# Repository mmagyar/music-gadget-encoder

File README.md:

# Music gadget base on STM32G070 MCU

# Modes of operation
 - Step sequencer
 - Midi controller
 
# Software
This project is built on a basic STM32Cube generated base, with using LL drivers.
TrueSTUDIO for STM32 is used for building and debugging.

# Hardware
The schematics and the pcb is designed with KiCad.
This is not a pcb that can be easily done at home, but most cheap chinease pcb manufaturers will be able to make them for you.
It uses 0805 SMD components, soldering this together is not for beginner.

# Picture of the prototype
In step sequencer mode:

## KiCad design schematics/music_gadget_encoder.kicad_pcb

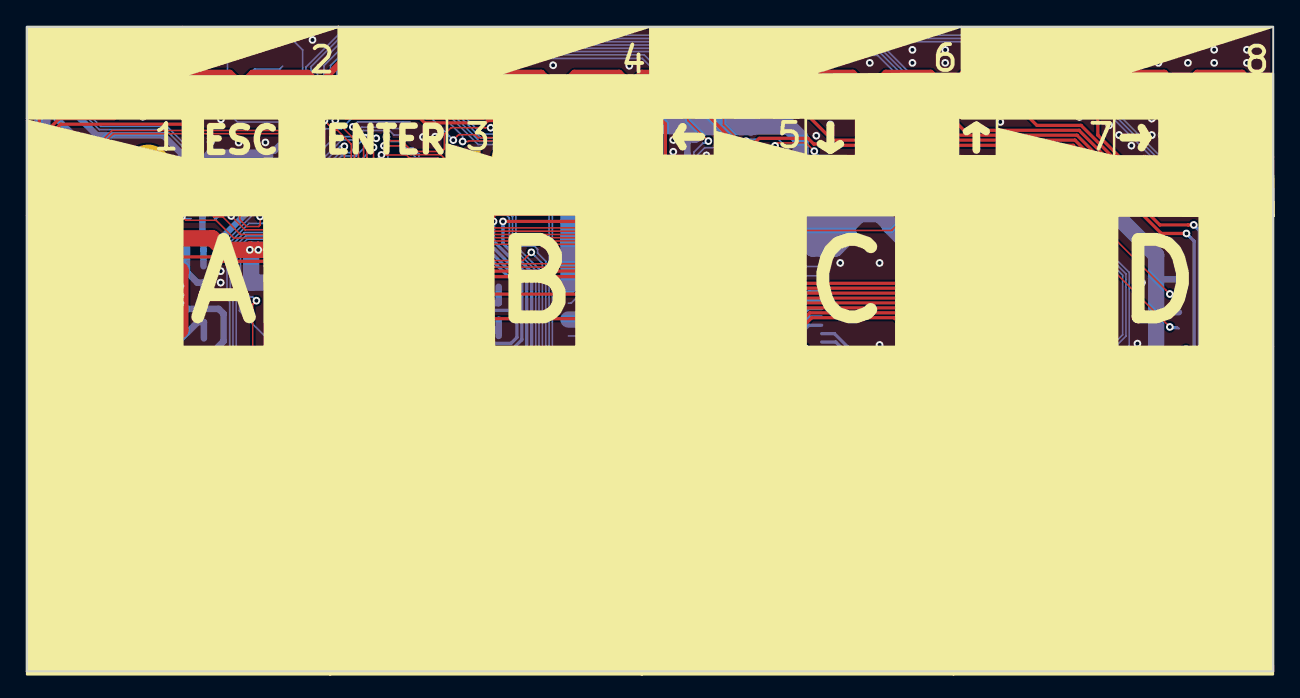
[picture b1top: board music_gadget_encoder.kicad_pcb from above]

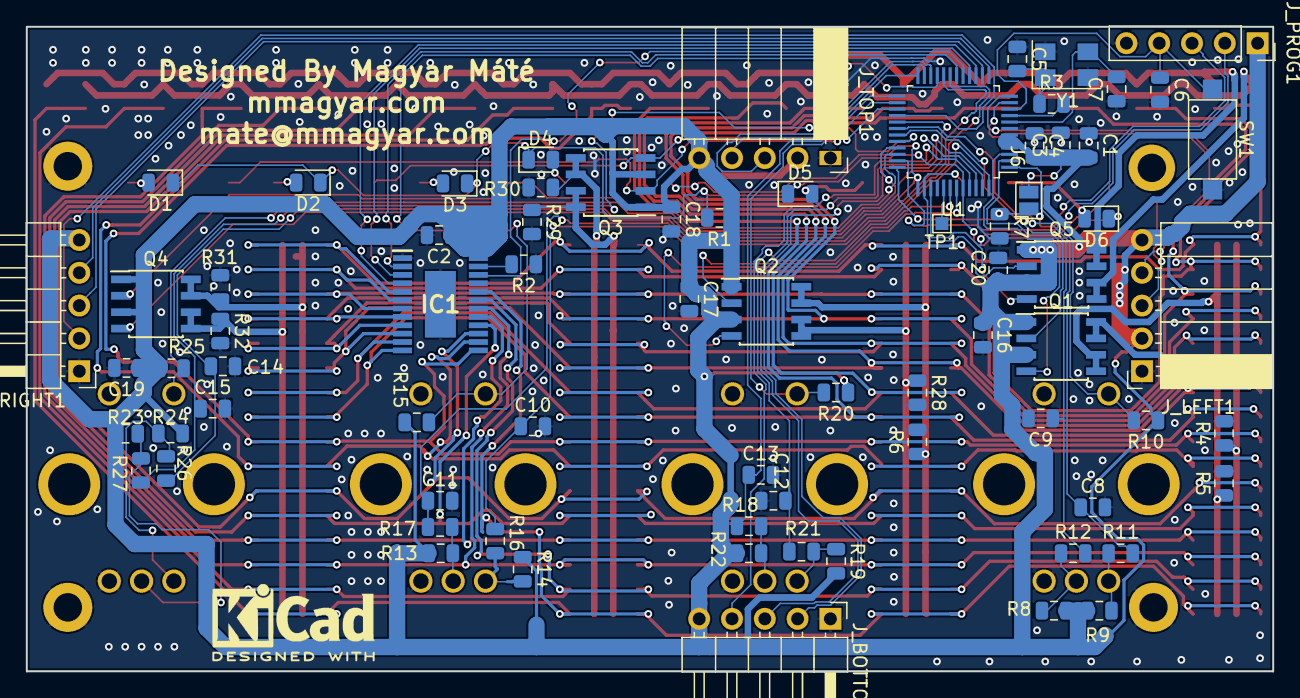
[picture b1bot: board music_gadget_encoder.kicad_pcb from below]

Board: 2 copper layers, 96.5 x 49.9 mm, 248 parts (74 on the bottom side), 87 nets.

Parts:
C1: 4.7u; C_0805_2012Metric
C2, C3, C4, C16, C17, C18, C19, C20: 100n; C_0805_2012Metric
C5, C7: 18pf; C_0805_2012Metric
C6: 100nf; C_0805_2012Metric
C8, C9, C10, C11, C12, C13, C14, C15: 10n; C_0805_2012Metric
D1, D2, D3, D4, D5, D6: DIODE; D_0805_2012Metric
D9, D10, D11, D12, D13, D14, D15, D16, D17, D18, D19, D20, D21, D22, D23, D24, D25, D26, D27, D28, D29, D30, D31, D32, D33, D34, D35, D36, D37, D38, D39, D40, D41, D42, D43, D44, D45, D46, D47, D48, D49, D50, D51, D52, D53, D54, D55, D56, D57, D58, D59, D60, D61, D62, D63, D64, D65, D66, D67, D68, D69, D70, D71, D72, D73, D74, D75, D76, D77, D78, D79, D80, D81, D82, D83, D84, D85, D86, D87, D88, D89, D90, D91, D92, D93, D94, D95, D96, D97, D98, D99, D100, D101, D102, D103, D104, D105, D106, D107, D108, D109, D110, D111, D112, D113, D114, D115, D116, D117, D118, D119, D120, D121, D122, D123, D124, D125, D126, D127, D128, D129, D130, D131, D132, D133, D134, D135, D136, D137, D138, D139, D140, D141, D142, D143, D144, D145, D146, D147, D148, D149, D150, D151, D152, D153, D154, D155, D156, D157, D158, D159, D160, D161, D162, D163, D164, D165, D166, D167, D168: LED; LED_0805_2012Metric_NO_SILKSCREEN
H1, H2, H3, H4: MountingHole_Pad; MountingHole_2.2mm_M2_DIN965_Pad
IC1: TLC5926IPWPR; SOP65P640X120-25N
J6: Conn_01x02_Male; SolderJumper-2_P1.3mm_Open_Pad1.0x1.5mm
J_BOTTOM1: Conn_01x05; PinHeader_1x05_P2.54mm_Horizontal
J_LEFT1: Conn_01x05; PinSocket_1x05_P2.54mm_Horizontal
J_PROG1: Conn_01x05; PinSocket_1x05_P2.54mm_Vertical
J_RIGHT1: Conn_01x05; PinHeader_1x05_P2.54mm_Horizontal
J_TOP1: Conn_01x05; PinSocket_1x05_P2.54mm_Horizontal
Q1, Q2, Q3, Q4, Q5: DMG9933USD-13; SOIC-8_3.9x4.9mm_P1.27mm
R1, R7: 10k; R_0805_2012Metric
R2: R; R_0805_2012Metric
R3: 390; R_0805_2012Metric
R4, R5, R6, R28, R29, R30, R31, R32: 1k; R_0805_2012Metric
R8, R9, R10, R11, R12, R13, R14, R15, R16, R17, R18, R19, R20, R21, R22, R23, R24, R25, R26, R27: 10K; R_0805_2012Metric
SW1, SW2, SW3, SW4, SW5, SW6, SW7: SW_Push; SW_SPST_CK_RS282G05A3
TP1: TestPoint; TestPoint_Pad_1.0x1.0mm
U1: STM32G070CBTx; LQFP-48_7x7mm_P0.5mm
U2, U3, U4, U5: PEC12R-4225F-S0024; ENCODER_PEC12R-4XXXF-SXXXX_1
Y1: Crystal_GND24; Crystal_SMD_5032-4Pin_5.0x3.2mm

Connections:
/BUTTONS: D1.1, D2.1, D3.1, D4.1, D5.1, D6.1, R1.2, U1.44
/ENC_A_0: C8.1, R11.2, U1.30
/ENC_A_1: C10.1, R16.2, U1.19
/ENC_A_2: C12.1, R21.2, U1.48
/ENC_A_3: C14.1, R26.2, U1.29
/ENC_B_0: C9.1, R12.2, U1.31
/ENC_B_1: C11.1, R17.2, U1.20
/ENC_B_2: C13.1, R22.2, U1.24
/ENC_B_3: C15.1, R27.2, U1.32
/ENC_S_0: R10.2, U1.1, U2.4
/ENC_S_1: R15.2, U1.21, U3.4
/ENC_S_2: R20.2, U1.25, U4.4
/ENC_S_3: R25.2, U1.33, U5.4
/LED_0: D9.1, D10.1, D41.1, D42.1, D73.1, D74.1, D105.1, D106.1, D137.1, D138.1, IC1.5
/LED_1: D11.1, D12.1, D43.1, D44.1, D75.1, D76.1, D107.1, D108.1, D139.1, D140.1, IC1.6
/LED_2: D13.1, D14.1, D45.1, D46.1, D77.1, D78.1, D109.1, D110.1, D141.1, D142.1, IC1.7
/LED_3: D15.1, D16.1, D47.1, D48.1, D79.1, D80.1, D111.1, D112.1, D143.1, D144.1, IC1.8
/LED_4: D17.1, D18.1, D49.1, D50.1, D81.1, D82.1, D113.1, D114.1, D145.1, D146.1, IC1.9
/LED_5: D19.1, D20.1, D51.1, D52.1, D83.1, D84.1, D115.1, D116.1, D147.1, D148.1, IC1.10
/LED_6: D21.1, D22.1, D53.1, D54.1, D85.1, D86.1, D117.1, D118.1, D149.1, D150.1, IC1.11
/LED_7: D23.1, D24.1, D55.1, D56.1, D87.1, D88.1, D119.1, D120.1, D151.1, D152.1, IC1.12
/LED_8: D25.1, D26.1, D57.1, D58.1, D89.1, D90.1, D121.1, D122.1, D153.1, D154.1, IC1.13
/LED_9: D27.1, D28.1, D59.1, D60.1, D91.1, D92.1, D123.1, D124.1, D155.1, D156.1, IC1.14
/LED_10: D29.1, D30.1, D61.1, D62.1, D93.1, D94.1, D125.1, D126.1, D157.1, D158.1, IC1.15
/LED_11: D31.1, D32.1, D63.1, D64.1, D95.1, D96.1, D127.1, D128.1, D159.1, D160.1, IC1.16
/LED_12: D33.1, D34.1, D65.1, D66.1, D97.1, D98.1, D129.1, D130.1, D161.1, D162.1, IC1.17
/LED_13: D35.1, D36.1, D67.1, D68.1, D99.1, D100.1, D131.1, D132.1, D163.1, D164.1, IC1.18
/LED_14: D37.1, D38.1, D69.1, D70.1, D101.1, D102.1, D133.1, D134.1, D165.1, D166.1, IC1.19
/LED_15: D39.1, D40.1, D71.1, D72.1, D103.1, D104.1, D135.1, D136.1, D167.1, D168.1, IC1.20
/LED_MUX_0: Q1.2, U1.2
/LED_MUX_1: Q1.4, U1.3
/LED_MUX_2: Q2.2, U1.42
/LED_MUX_3: Q2.4, U1.43
/LED_MUX_4: Q3.2, SW2.1, U1.26
/LED_MUX_5: Q3.4, SW3.1, U1.27
/LED_MUX_6: Q4.2, SW4.1, U1.34
/LED_MUX_7: Q4.4, SW5.1, U1.37
/LED_MUX_8: Q5.2, SW6.1, U1.38
/LED_MUX_9: Q5.4, SW7.1, U1.39
/MISO: IC1.22, U1.17
/MOSI: IC1.2, U1.18
/NSS: IC1.4, U1.15
/RESET: C6.1, J_PROG1.4, SW1.1, U1.10
/SCLK: IC1.3, U1.16
/SWCLK: J6.1, J_PROG1.3, R7.1, U1.36
/SWDIO: J_PROG1.2, U1.35
/USART1_DETECT: J_BOTTOM1.2, U1.47
/USART1_RX: J_BOTTOM1.3, U1.46
/USART1_TX: J_BOTTOM1.4, U1.45
/USART2_DETECT: J_RIGHT1.2, U1.28
/USART2_RX: J_RIGHT1.3, U1.14
/USART2_TX: J_RIGHT1.4, U1.13
/USART3_RX: J_TOP1.4, U1.23
/USART3_TX: J_TOP1.3, U1.22
/USART4_RX: J_LEFT1.4, U1.12
/USART4_TX: J_LEFT1.3, U1.11
GND: C1.1, C2.2, C3.2, C4.1, C5.1, C6.2, C7.1, C8.2, C9.2, C10.2, C11.2, C12.2, C13.2, C14.2, C15.2, C16.2, C17.2, C18.2, C19.2, C20.2, H1.1, H2.1, H3.1, H4.1, IC1.1, IC1.21, IC1.25, J_BOTTOM1.1, J_LEFT1.1, J_PROG1.5, J_RIGHT1.1, J_TOP1.1, R2.1, R4.2, R5.2, R6.2, R7.2, R28.2, R29.2, R30.2, R31.2, R32.2, SW1.2, U1.7, U2.2, U2.5, U3.2, U3.5, U4.2, U4.5, U5.2, U5.5, Y1.2, Y1.4
unnamed: C5.2, R3.1, Y1.1
unnamed: C7.2, U1.8, Y1.3
unnamed: D1.2, SW2.2
unnamed: D2.2, SW3.2
unnamed: D3.2, SW4.2
unnamed: D4.2, SW5.2
unnamed: D5.2, SW6.2
unnamed: D6.2, SW7.2
unnamed: D10.2, D12.2, D14.2, D16.2, D18.2, D20.2, D22.2, D24.2, D26.2, D28.2, D30.2, D32.2, D34.2, D36.2, D38.2, D40.2, Q1.7, Q1.8, R4.1
unnamed: D9.2, D11.2, D13.2, D15.2, D17.2, D19.2, D21.2, D23.2, D25.2, D27.2, D29.2, D31.2, D33.2, D35.2, D37.2, D39.2, Q1.5, Q1.6, R5.1
unnamed: D41.2, D43.2, D45.2, D47.2, D49.2, D51.2, D53.2, D55.2, D57.2, D59.2, D61.2, D63.2, D65.2, D67.2, D69.2, D71.2, Q2.5, Q2.6, R28.1
unnamed: D42.2, D44.2, D46.2, D48.2, D50.2, D52.2, D54.2, D56.2, D58.2, D60.2, D62.2, D64.2, D66.2, D68.2, D70.2, D72.2, Q2.7, Q2.8, R6.1
unnamed: D74.2, D76.2, D78.2, D80.2, D82.2, D84.2, D86.2, D88.2, D90.2, D92.2, D94.2, D96.2, D98.2, D100.2, D102.2, D104.2, Q3.7, Q3.8, R29.1
unnamed: D73.2, D75.2, D77.2, D79.2, D81.2, D83.2, D85.2, D87.2, D89.2, D91.2, D93.2, D95.2, D97.2, D99.2, D101.2, D103.2, Q3.5, Q3.6, R30.1
unnamed: D105.2, D107.2, D109.2, D111.2, D113.2, D115.2, D117.2, D119.2, D121.2, D123.2, D125.2, D127.2, D129.2, D131.2, D133.2, D135.2, Q4.5, Q4.6, R32.1
unnamed: D106.2, D108.2, D110.2, D112.2, D114.2, D116.2, D118.2, D120.2, D122.2, D124.2, D126.2, D128.2, D130.2, D132.2, D134.2, D136.2, Q4.7, Q4.8, R31.1
unnamed: D137.2, D139.2, D141.2, D143.2, D145.2, D147.2, D149.2, D151.2, D153.2, D155.2, D157.2, D159.2, D161.2, D163.2, D165.2, D167.2, Q5.5, Q5.6
unnamed: D138.2, D140.2, D142.2, D144.2, D146.2, D148.2, D150.2, D152.2, D154.2, D156.2, D158.2, D160.2, D162.2, D164.2, D166.2, D168.2, Q5.7, Q5.8
unnamed: IC1.23, R2.2
unnamed: R3.2, U1.9
unnamed: R9.2, R11.1, U2.1
unnamed: R8.2, R12.1, U2.3
unnamed: R13.2, R17.1, U3.3
unnamed: R14.2, R16.1, U3.1
unnamed: R18.2, R22.1, U4.3
unnamed: R19.2, R21.1, U4.1
unnamed: R23.2, R27.1, U5.3
unnamed: R24.2, R26.1, U5.1
unnamed: TP1.1, U1.41
VCC: C1.2, C2.1, C3.1, C4.2, C16.1, C17.1, C18.1, C19.1, C20.1, IC1.24, J6.2, J_BOTTOM1.5, J_LEFT1.2, J_LEFT1.5, J_PROG1.1, J_RIGHT1.5, J_TOP1.2, J_TOP1.5, Q1.1, Q1.3, Q2.1, Q2.3, Q3.1, Q3.3, Q4.1, Q4.3, Q5.1, Q5.3, R1.1, R8.1, R9.1, R10.1, R13.1, R14.1, R15.1, R18.1, R19.1, R20.1, R23.1, R24.1, R25.1, U1.4, U1.5, U1.6

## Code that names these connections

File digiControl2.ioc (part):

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Mcu.Name=STM32G070CBTx
Mcu.Package=LQFP48
Mcu.UserName=STM32G070CBTx
PA0.Mode=Asynchronous
PA0.Signal=USART4_TX
PA1.Mode=Asynchronous
PA1.Signal=USART4_RX
PA10.GPIOParameters=GPIO_Label
PA10.GPIO_Label=ENC_B_3
PA10.Signal=GPIO_Input
PA11\ [PA9].GPIOParameters=GPIO_Label
PA11\ [PA9].GPIO_Label=ENC_S_3
PA11\ [PA9].Signal=GPIO_Input
PA12\ [PA10].GPIOParameters=GPIO_Speed,GPIO_Label
PA12\ [PA10].GPIO_Label=LED_MUX_6
PA12\ [PA10].GPIO_Speed=GPIO_SPEED_FREQ_VERY_HIGH
PA12\ [PA10].Signal=GPIO_Output
PA13.Mode=Serial_Wire
PA13.Signal=SYS_SWDIO
PA14-BOOT0.Mode=Serial_Wire
PA14-BOOT0.Signal=SYS_SWCLK
PA15.GPIOParameters=GPIO_Speed,GPIO_Label
PA15.GPIO_Label=LED_MUX_7
PA15.GPIO_Speed=GPIO_SPEED_FREQ_VERY_HIGH
PA15.Signal=GPIO_Output
PA2.Mode=Asynchronous
PA2.Signal=USART2_TX
PA3.Mode=Asynchronous
PA3.Signal=USART2_RX
PA4.GPIOParameters=GPIO_Speed
PA4.GPIO_Speed=GPIO_SPEED_FREQ_HIGH
PA4.Mode=NSS_Signal_Hard_Output
PA4.Signal=SPI1_NSS
PA5.GPIOParameters=GPIO_Speed
PA5.GPIO_Speed=GPIO_SPEED_FREQ_HIGH
PA5.Mode=TX_Only_Simplex_Unidirect_Master
PA5.Signal=SPI1_SCK
PA6.Signal=SPI1_MISO
PA7.GPIOParameters=GPIO_Speed
PA7.GPIO_Speed=GPIO_SPEED_FREQ_HIGH
PA7.Mode=TX_Only_Simplex_Unidirect_Master
PA7.Signal=SPI1_MOSI
PA8.GPIOParameters=GPIO_Label
PA8.GPIO_Label=USART2_DETECT
PA8.Signal=GPIO_Input
PA9.GPIOParameters=GPIO_Label
PA9.GPIO_Label=ENC_A_3
PA9.Signal=GPIO_Input
PB0.GPIOParameters=GPIO_Label
PB0.GPIO_Label=ENC_A_2
PB0.Signal=GPIO_Input
PB1.GPIOParameters=GPIO_Label
PB1.GPIO_Label=ENC_B_2
PB1.Signal=GPIO_Input
PB10.Mode=Asynchronous
PB10.Signal=USART3_TX
PB11.Mode=Asynchronous
PB11.Signal=USART3_RX
PB12.GPIOParameters=GPIO_Label
PB12.GPIO_Label=ENC_B_1
PB12.Signal=GPIO_Input
PB13.GPIOParameters=GPIO_Label
PB13.GPIO_Label=ENC_S_1
PB13.Signal=GPIO_Input
PB14.GPIOParameters=GPIO_Speed,GPIO_Label
PB14.GPIO_Label=LED_MUX_4
PB14.GPIO_Speed=GPIO_SPEED_FREQ_VERY_HIGH
PB14.Signal=GPIO_Output
PB15.GPIOParameters=GPIO_Speed,GPIO_Label
PB15.GPIO_Label=LED_MUX_5
PB15.GPIO_Speed=GPIO_SPEED_FREQ_VERY_HIGH
PB15.Signal=GPIO_Output
PB2.GPIOParameters=GPIO_Label
PB2.GPIO_Label=ENC_S_2
PB2.Signal=GPIO_Input
PB3.GPIOParameters=GPIO_Speed,GPIO_Label
PB3.GPIO_Label=LED_MUX_2
PB3.GPIO_Speed=GPIO_SPEED_FREQ_VERY_HIGH
PB3.Signal=GPIO_Output
PB4.GPIOParameters=GPIO_Speed,GPIO_Label
PB4.GPIO_Label=LED_MUX_3
PB4.GPIO_Speed=GPIO_SPEED_FREQ_VERY_HIGH
PB4.Signal=GPIO_Output
PB5.GPIOParameters=GPIO_Label
PB5.GPIO_Label=BUTTONS
PB5.Signal=GPIO_Input
PB6.Mode=Asynchronous
PB6.Signal=USART1_TX
PB7.Mode=Asynchronous
PB7.Signal=USART1_RX
PB8.GPIOParameters=GPIO_Label
PB8.GPIO_Label=USART1_DETECT
PB8.Signal=GPIO_Input
PB9.GPIOParameters=GPIO_Label
PB9.GPIO_Label=ENC_A_1
PB9.Signal=GPIO_Input
PC13.GPIOParameters=GPIO_Label
PC13.GPIO_Label=ENC_S_0
PC13.Signal=GPIO_Input
PC14-OSC32_IN\ (PC14).GPIOParameters=GPIO_Label
PC14-OSC32_IN\ (PC14).GPIO_Label=LED_MUX_0
PC14-OSC32_IN\ (PC14).Signal=GPIO_Output
PC15-OSC32_OUT\ (PC15).GPIOParameters=GPIO_Label
PC15-OSC32_OUT\ (PC15).GPIO_Label=LED_MUX_1
PC15-OSC32_OUT\ (PC15).Signal=GPIO_Output
PC6.GPIOParameters=GPIO_Label
PC6.GPIO_Label=ENC_A_0
PC6.Signal=GPIO_Input
PC7.GPIOParameters=GPIO_Label
PC7.GPIO_Label=ENC_B_0
PC7.Signal=GPIO_Input
PD0.GPIOParameters=GPIO_Speed,GPIO_Label
PD0.GPIO_Label=LED_MUX_8
PD0.GPIO_Speed=GPIO_SPEED_FREQ_VERY_HIGH
PD0.Signal=GPIO_Output
PD1.GPIOParameters=GPIO_Speed,GPIO_Label
PD1.GPIO_Label=LED_MUX_9
PD1.GPIO_Speed=GPIO_SPEED_FREQ_VERY_HIGH
PD1.Signal=GPIO_Output
PD3.GPIOParameters=GPIO_Speed,GPIO_Label
PD3.GPIO_Label=TEST_POINT
PD3.GPIO_Speed=GPIO_SPEED_FREQ_VERY_HIGH
PD3.Signal=GPIO_Output
PF0-OSC_IN\ (PF0).Mode=HSE-External-Oscillator
PF0-OSC_IN\ (PF0).Signal=RCC_OSC_IN
PF1-OSC_OUT\ (PF1).Mode=HSE-External-Oscillator
PF1-OSC_OUT\ (PF1).Signal=RCC_OSC_OUT
RCC.HSE_VALUE=8000000
RCC.SYSCLKFreq_VALUE=64000000
RCC.SYSCLKSource=RCC_SYSCLKSOURCE_PLLCLK
board=custom

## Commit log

2019-04-23 add submodule
2019-04-23 Use usart 3 for midi
2019-04-23 send midi
2019-04-27 add schematics
2019-05-05 refactor
2019-05-05 add midi controller mode
2019-05-05 Add crc module
2019-05-07 add crc and update utils
2019-05-07 update stm32 cube project with crc settings
2019-05-10 intial intercom implementation
2019-05-10 add serialization and deserialization based on structs
2019-05-14 update pcb
2019-05-16 update communication
2019-05-16 fix message receiving
2019-05-17 update intercom
2019-05-18 update mux for more consistent on time
2019-05-18 putchar for printing don't need a buffer
2019-05-18 update error printing
2019-05-18 refactor renaming
2019-05-18 update circular buffer util
2019-05-18 update to stm32cubeide from truestudio
2019-05-23 update circular buffer and crc
2019-05-23 forward messages
2019-05-24 add address broadcasting for device discovery
